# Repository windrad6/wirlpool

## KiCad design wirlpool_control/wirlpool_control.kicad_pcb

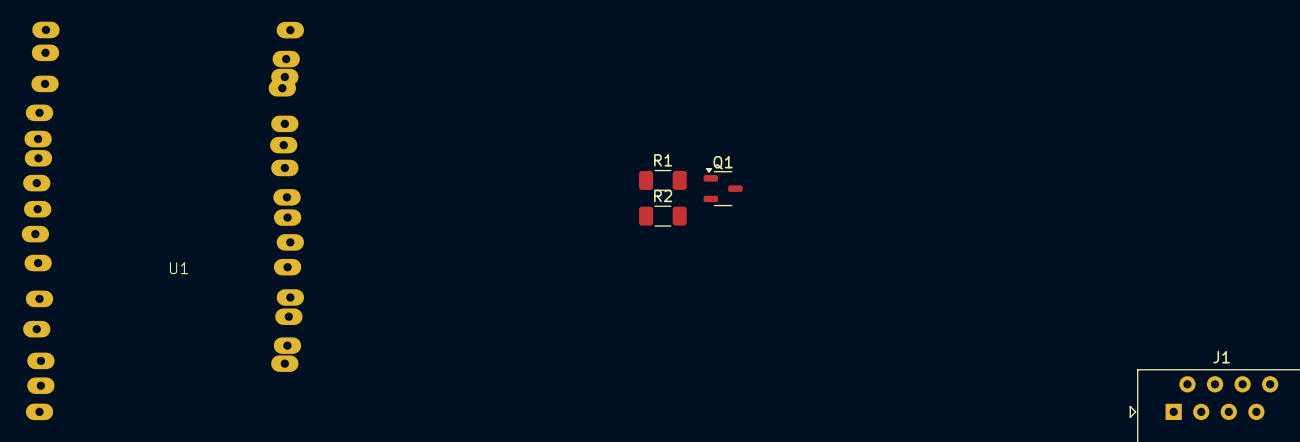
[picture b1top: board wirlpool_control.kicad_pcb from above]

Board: 2 copper layers, 5 parts (0 on the bottom side), 3 nets, no tracks yet.

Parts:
J1: RJ45; RJ45_Amphenol_54602-x08_Horizontal
Q1: IRLML2502; SOT-23-3
R1: 10; R_1206_3216Metric_Pad1.30x1.75mm_HandSolder
R2: 10k; R_1206_3216Metric_Pad1.30x1.75mm_HandSolder
U1: ESP32_dev

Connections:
/OUT1: R1.1, U1.27 (D2)
GND: Q1.2 (S), R2.1, U1.2 (GND), U1.29 (GND)
unnamed: Q1.1 (G), R1.2, R2.2

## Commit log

2024-05-20 inital
